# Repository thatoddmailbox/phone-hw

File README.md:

# phone-hw
The hardware (schematic, PCB, Gerbers) portion of a [phone I built](https://github.com/thatoddmailbox/phone). You might also want to see [the firmware](https://github.com/thatoddmailbox/phone-fw).

Uses an Espressif ESP32-WROVER module as main CPU + WiFi/Bluetooth, a Quectel M26 modem for GSM and GPRS data, and a Quectel L80 module for GPS.

If you're curious, a [PDF schematic](./mfg/phone-hw.pdf) is available.

## Things that would be nice in a future version
Also see the [issues page](https://github.com/thatoddmailbox/phone-hw/issues) for more specific bugs with the latest revision.
* Figure out a different input method, since the current switch is EOL by the manufacturer. The ESP32 probably won't be able to run a full touchscreen interface smoothly, but switches like the one currently used are not very popular...
* Using a different module for GPS since the L80 has a built-in antenna that is the main contributor to the phone's thickness.
* Upgrading the modem to something that can do a bit more than 2G, though this might require a different communication mechanism than a simple UART
* Built-in speakers and microphone instead of requiring a Bluetooth headset
* 3.5mm headphone/headset jack - would require an external I2S DAC/ADC for best performance?
* CPU upgrade? The ESP32 is definitely powerful enough (for now...), but it's short on pins, which is why certain features had to be cut. Maybe ditch the extra 4MB SRAM and use those pins? (the extra RAM is currently unused by the firmware) However, it would also be nice to get a chip that could do USB host and/or device, especially if a future modem wants a USB connection
* USB-PD charging?? Probably not realistic, since it would require a battery that could safely handle the higher currents

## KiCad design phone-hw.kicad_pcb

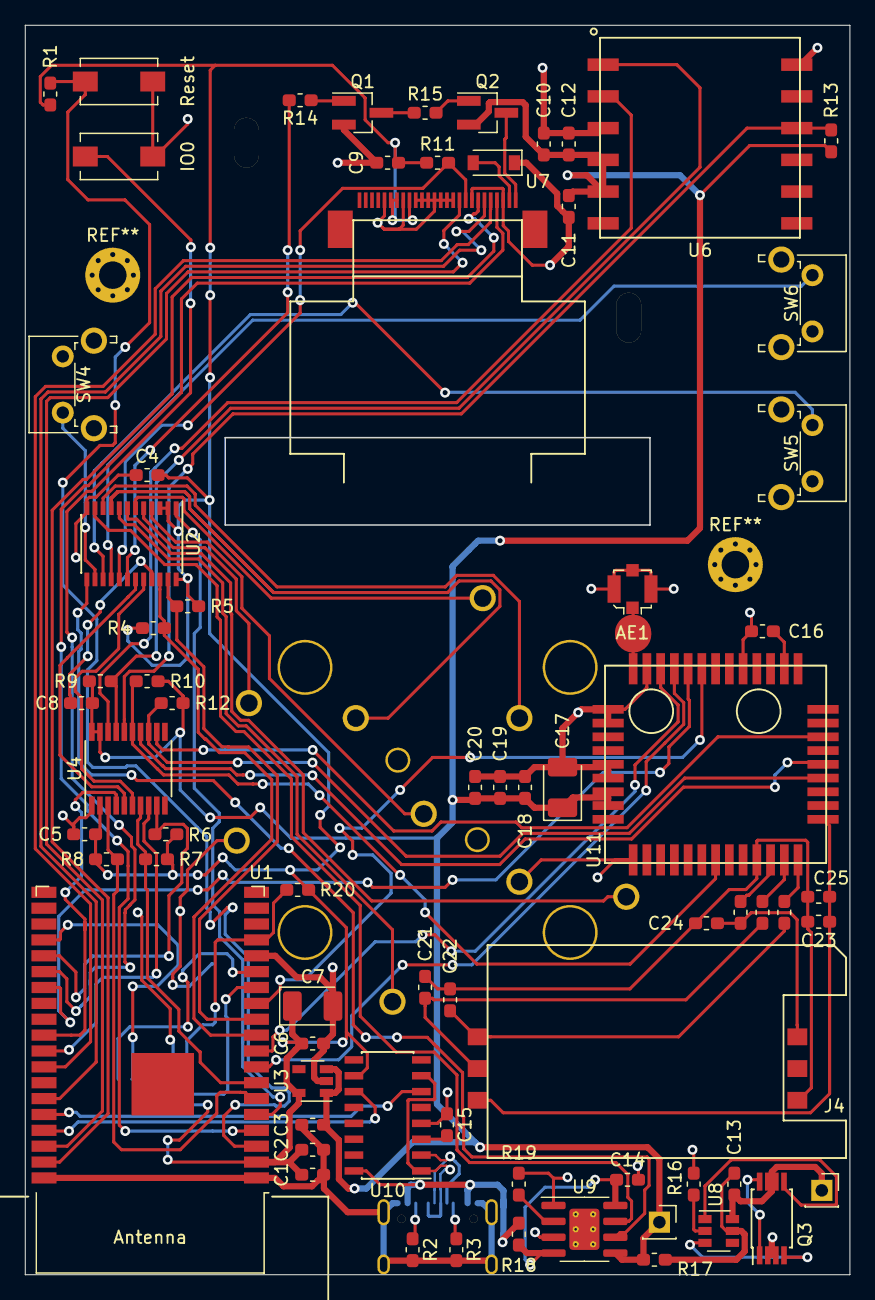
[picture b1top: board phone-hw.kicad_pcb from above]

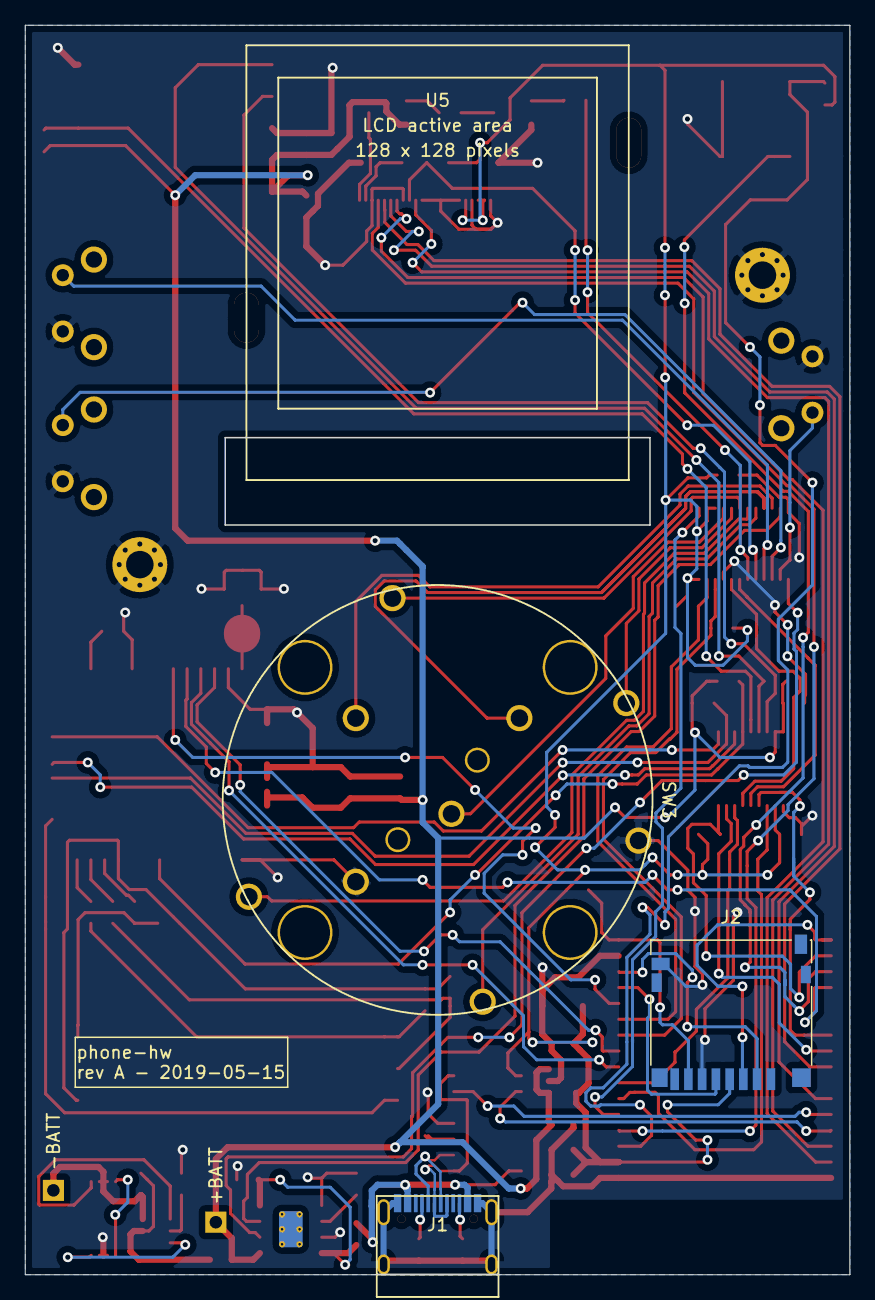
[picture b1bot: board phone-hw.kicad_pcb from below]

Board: 2 copper layers, 65.9 x 99.9 mm, 74 parts (4 on the bottom side), 80 nets.

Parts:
AE1: Antenna_Shield; U.FL_Molex_MCRF_73412-0110_Vertical
C1: 22uF; C_0603_1608Metric_Pad1.05x0.95mm_HandSolder
C2, C4, C5, C8, C9, C11, C12, C13, C18, C25: 0.1uF; C_0603_1608Metric_Pad1.05x0.95mm_HandSolder
C3, C15: 1uF; C_0603_1608Metric_Pad1.05x0.95mm_HandSolder
C6, C16: 4.7uF; C_0603_1608Metric_Pad1.05x0.95mm_HandSolder
C7, C17: 100uF; CP_EIA-3528-15_AVX-H_Pad1.50x2.35mm_HandSolder
C10, C14: 10uF; C_0603_1608Metric_Pad1.05x0.95mm_HandSolder
C19: 10pF; C_0603_1608Metric_Pad1.05x0.95mm_HandSolder
C20, C21, C22, C23, C24: 33pF; C_0603_1608Metric_Pad1.05x0.95mm_HandSolder
J1: USB_C_Receptacle_USB2.0; U262-16XN-4BVC11
J2: Micro_SD_Card; microSD_HC_Hirose_DM3D-SF
J4: SIM_Card; 7112S0815X19LF
J5: BATT+; PinSocket_1x01_P2.54mm_Vertical
J6: BATT-; PinSocket_1x01_P2.54mm_Vertical
Q1: BC847BLT3G; SOT-23_Handsoldering
Q2: S9015; SOT-23_Handsoldering
Q3: RU8205G; TSSOP-8_4.4x3mm_P0.65mm
R1, R4, R5, R6, R7, R8, R9, R10, R11, R12, R13, R20: 10k; R_0603_1608Metric_Pad1.05x0.95mm_HandSolder
R2, R3: 5.1k; R_0603_1608Metric_Pad1.05x0.95mm_HandSolder
R14, R15, R16: 1k; R_0603_1608Metric_Pad1.05x0.95mm_HandSolder
R17: 100; R_0603_1608Metric_Pad1.05x0.95mm_HandSolder
R18: 0.4; R_0603_1608Metric_Pad1.05x0.95mm_HandSolder
R19: 1.2k; R_0603_1608Metric_Pad1.05x0.95mm_HandSolder
R22, R23, R24: 22; R_0603_1608Metric_Pad1.05x0.95mm_HandSolder
SW1, SW2: SW_Push; SW_SPST_EVQPE1
SW3: TSWB-3N-CB
SW4: Lock; SW_Tactile_SPST_Angled_PTS645Vx58-2LFS
SW5: VolUp; SW_Tactile_SPST_Angled_PTS645Vx58-2LFS
SW6: VolDown; SW_Tactile_SPST_Angled_PTS645Vx58-2LFS
U1: ESP32-WROVER
U2: PCAL6416A; TSSOP-24_4.4x7.8mm_P0.65mm
U3: XC6222B281MR-G; SOT-23-5
U4: NVT2008; TSSOP-20_4.4x6.5mm_P0.65mm
U5: ER-TFT1.44-1; ER-TFT1.44-1-FOLD
U6: L80-R
U7: NSI45015WT1G; D_SOD-123
U8: DW01A; SOT-23-6
U9: TP4056; SOIC-8-1EP_3.9x4.9mm_P1.27mm_EP2.41x3.3mm_ThermalVias
U10: HT42B534; SOIC-16_3.9x9.9mm_P1.27mm
U11: M26

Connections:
+BATT: C3.1, C8.1, C10.1, C11.1, C12.1, C17.1, C18.1, C19.1, C20.1, J5.1, Q2.2, R9.1, R10.2, R12.2, R13.2, R17.2, U3.1, U3.3, U4.19, U4.20, U6.4, U6.5, U9.5, U11.42, U11.43
/Battery protection/GND_IN: C13.1, J6.1, Q3.6, Q3.7, U8.6
BATT_~CHRG: U2.11, U9.7
BATT_~STDBY: U2.13, U9.6
GND_OUT: AE1.2, C1.2, C2.2, C3.2, C4.2, C5.2, C6.2, C7.2, C8.2, C9.2, C10.2, C11.2, C12.2, C14.2, C15.1, C16.2, C17.2, C18.2, C19.2, C20.2, J1.A1, J1.B1, J1.S1, J2.6, J2.9, Q1.2, Q3.2, Q3.3, R2.2, R3.2, R16.1, R19.2, SW1.2, SW2.2, SW3.CA, SW3.CB, SW4.2, SW5.2, SW6.2, U1.1, U1.15, U1.38, U2.12, U2.21, U3.2, U4.1, U5.3, U5.8, U5.11, U5.12, U5.13, U5.14, U5.15, U5.16, U5.17, U5.19, U5.22, U6.3, U6.12, U7.1, U9.1, U9.3, U10.4, U11.1, U11.27, U11.34, U11.36, U11.37, U11.40, U11.41
GPS_RESET: R13.1, U4.16, U6.10
GPS_RESET_2.8: U2.19, U4.5
GPS_RXD: R9.2, U4.17, U6.1
GPS_TXD: U4.18, U6.2
GSM_PWRKEY: R10.1, U4.15, U11.7
GSM_PWRKEY_2.8: U2.20, U4.6
GSM_RI: U4.12, U11.20
GSM_RI_2.8: R6.2, U1.24, U4.9
GSM_RXD: R12.1, U4.13, U11.17
GSM_TXD: U4.14, U11.18
I2C_SCL: R4.2, U1.10, U2.22
I2C_SDA: R5.2, U1.11, U2.23
INPUT_A: SW3.A, U2.9
INPUT_B: SW3.B, U2.10
INPUT_INT: U1.5, U2.1
INPUT_S1: SW3.S1, U2.4
INPUT_S2: SW3.S2, U2.5
INPUT_S3: SW3.S3, U2.6
INPUT_S4: SW3.S4, U2.7
INPUT_S5: SW3.S5, U2.8
LCD_BL: R14.2, U2.18
LCD_DC: U1.37, U5.7
LCD_RESET: R11.1, U2.17, U5.9
LCD_SCL: U1.33, U5.6
LCD_SDA: U1.36, U5.10
LCD_TE: U1.4, U5.4
LCD_~CS: U1.31, U5.5
unnamed: AE1.1, U11.35
unnamed: C13.2, R17.1, U8.5
unnamed: C14.1, R18.2, U9.4, U9.8
unnamed: C15.2, U10.3
unnamed: C16.1, U11.24
unnamed: C21.1, C22.1, C23.1, C24.1, C25.2, J4.5, U11.10
unnamed: C21.2, J4.2, R22.1
unnamed: C22.2, J4.3, R23.1
unnamed: C23.2, C25.1, J4.1, U11.14
unnamed: C24.2, J4.7, R24.1
unnamed: J1.A5, R3.1
unnamed: J1.B5, R2.1
unnamed: Q1.1, R14.1
unnamed: Q1.3, R15.2
unnamed: Q2.1, R15.1
unnamed: Q2.3, U5.1
unnamed: Q3.1, Q3.8
unnamed: Q3.4, U8.3
unnamed: Q3.5, U8.1
unnamed: R1.2, SW1.1, U1.3
unnamed: R16.2, U8.2
unnamed: R19.1, U9.2
unnamed: R22.2, U11.12
unnamed: R23.2, U11.13
unnamed: R24.2, U11.11
unnamed: SW2.1, U1.25
unnamed: SW4.1, U2.14
unnamed: SW5.1, U2.15
unnamed: SW6.1, U2.16
unnamed: U5.2, U7.2
PCM_CLK: U1.12, U11.30
PCM_IN: U1.8, U11.32
PCM_OUT: U1.9, U11.33
PCM_SYNC: U1.26, U11.31
SD_CLK: J2.5, U1.13
SD_MISO: J2.7, R20.2, U1.16
SD_MOSI: J2.3, U1.23
SD_~CS: J2.2, U1.14
UART0_RX: U1.34, U10.6
UART0_TX: U1.35, U10.11
UART1_RX: R8.2, U1.6, U4.3
UART1_TX: U1.29, U4.4
UART2_RX: R7.2, U1.7, U4.7
UART2_TX: U1.30, U4.8
USB_D+: J1.A6, J1.B6, U10.1, U10.7
USB_D-: J1.A7, J1.B7, U10.2
VBUS: J1.A4, J1.B4, R18.1, U10.16
VDD: C1.1, C2.1, C4.1, C5.1, C6.1, C7.1, C9.1, J2.4, R1.1, R4.1, R5.1, R6.1, R7.1, R8.1, R11.2, R20.1, U1.2, U2.2, U2.3, U2.24, U3.5, U4.2, U5.18, U5.20, U5.21, U10.10

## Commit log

2019-05-14 commit current eval board schematic
2019-05-14 fix label directions for some signals
2019-05-14 add some extra capacitance to the 2.8v line
2019-05-14 clear existing annotations from schematic
2019-05-14 fix battery status line to be pulled up to 2.8v, not +vbat
2019-05-14 fix lcd backlight circuit to use +batt instead of 2.8v for the backlight
2019-05-14 add tp4056 symbol
2019-05-14 upgrade charge circuit to use tp4056, allowing the battery to charge faster without the charger throttling itself
2019-05-14 increase size of pads on sim card connector
2019-05-14 add holes for bumps on back of tft scren
2019-05-14 add folded footprint of tft lcd
2019-05-14 set schematic to use folded display
2019-05-14 add symbol for pcal6416a
2019-05-14 switch i/o expander to larger version, moving signals off esp32
2019-05-14 add buttons and connect pcm interface of modem to esp32
2019-05-14 connect RI to esp32
2019-05-14 fix pin type of BAT pin on tp4056
2019-05-15 annotate schematic and tweak some footprint associations
2019-05-15 tweak
2019-05-15 update gitignore
2019-05-15 remove DS_Store
2019-05-15 battery charger status lines don't need pullups, as they're built-in to i/o expander
2019-05-15 change battery to use two different connectors instead of a small pin header
2019-05-15 remove debug port for modem
2019-05-15 tweak some footprint associations
2019-05-15 start pcb with placed components
2019-05-15 remove jtag port and move some other things around
2019-05-16 add sd card to schematic
2019-05-16 route pcb
2019-05-16 add mounting holes
2019-05-16 move mounting holes
2019-05-16 add silkscreen info and battery indicators
2019-05-16 add names of buttons to silkscreen
2019-05-16 connect mounting holes to ground
2019-05-16 add gerbers
2019-09-30 add README
2020-08-29 link to main phone project
2020-08-29 add LICENSE
